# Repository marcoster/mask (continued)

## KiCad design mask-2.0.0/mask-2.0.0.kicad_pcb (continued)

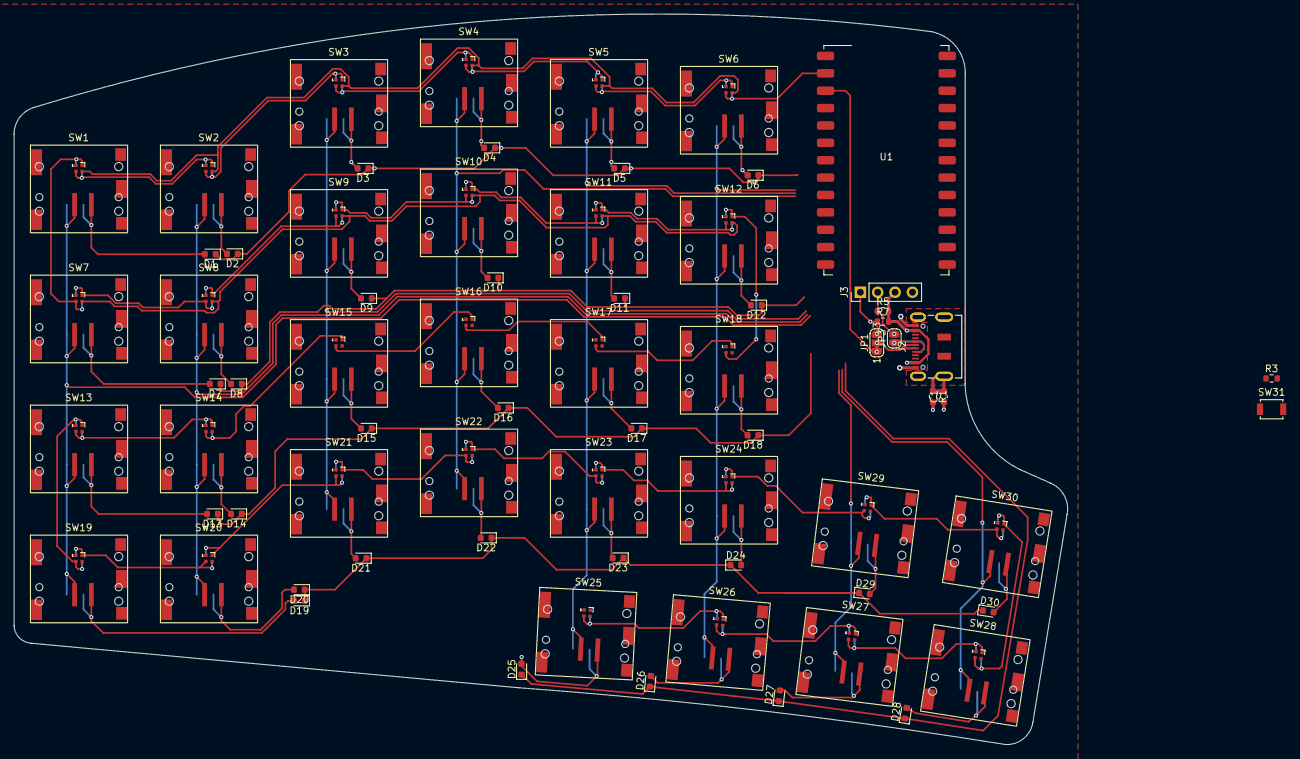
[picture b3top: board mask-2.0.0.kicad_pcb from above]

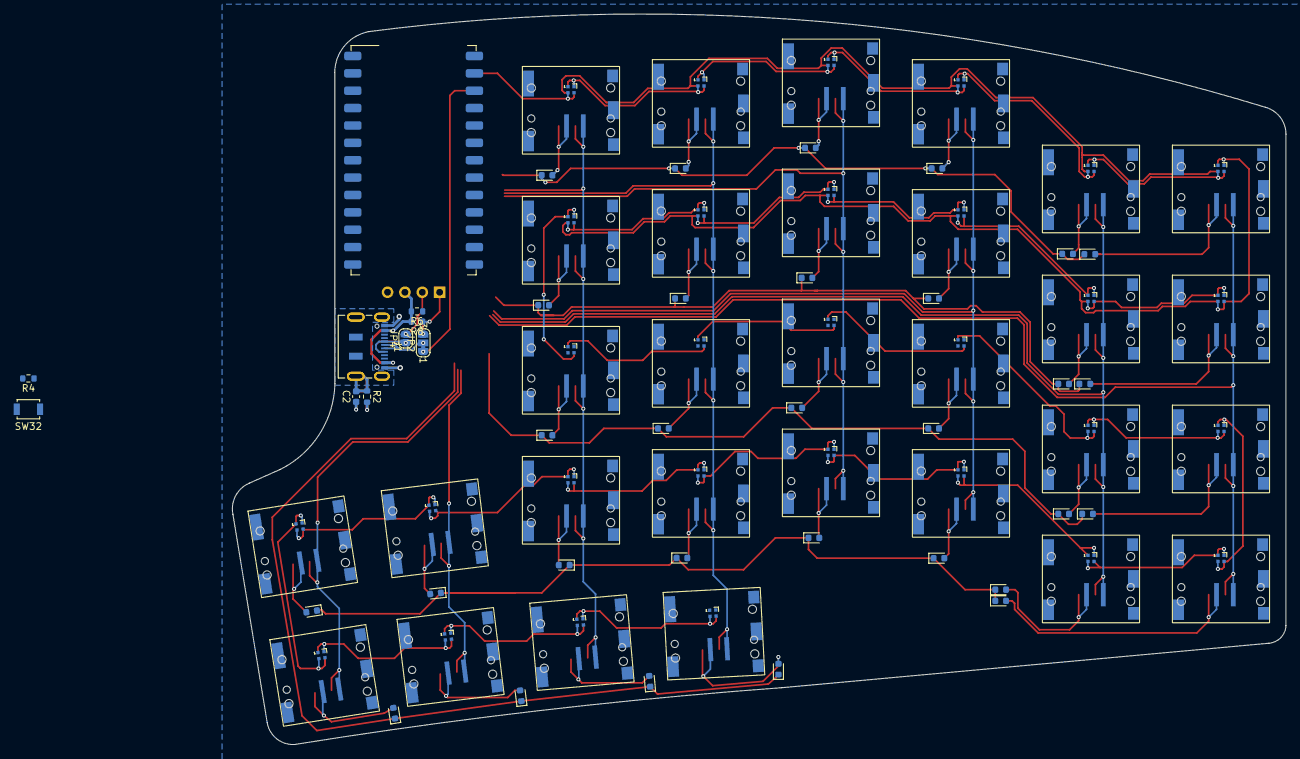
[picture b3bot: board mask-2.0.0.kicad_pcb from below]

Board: 2 copper layers, 154.0 x 106.8 mm, 80 parts (9 on the bottom side), 83 nets.

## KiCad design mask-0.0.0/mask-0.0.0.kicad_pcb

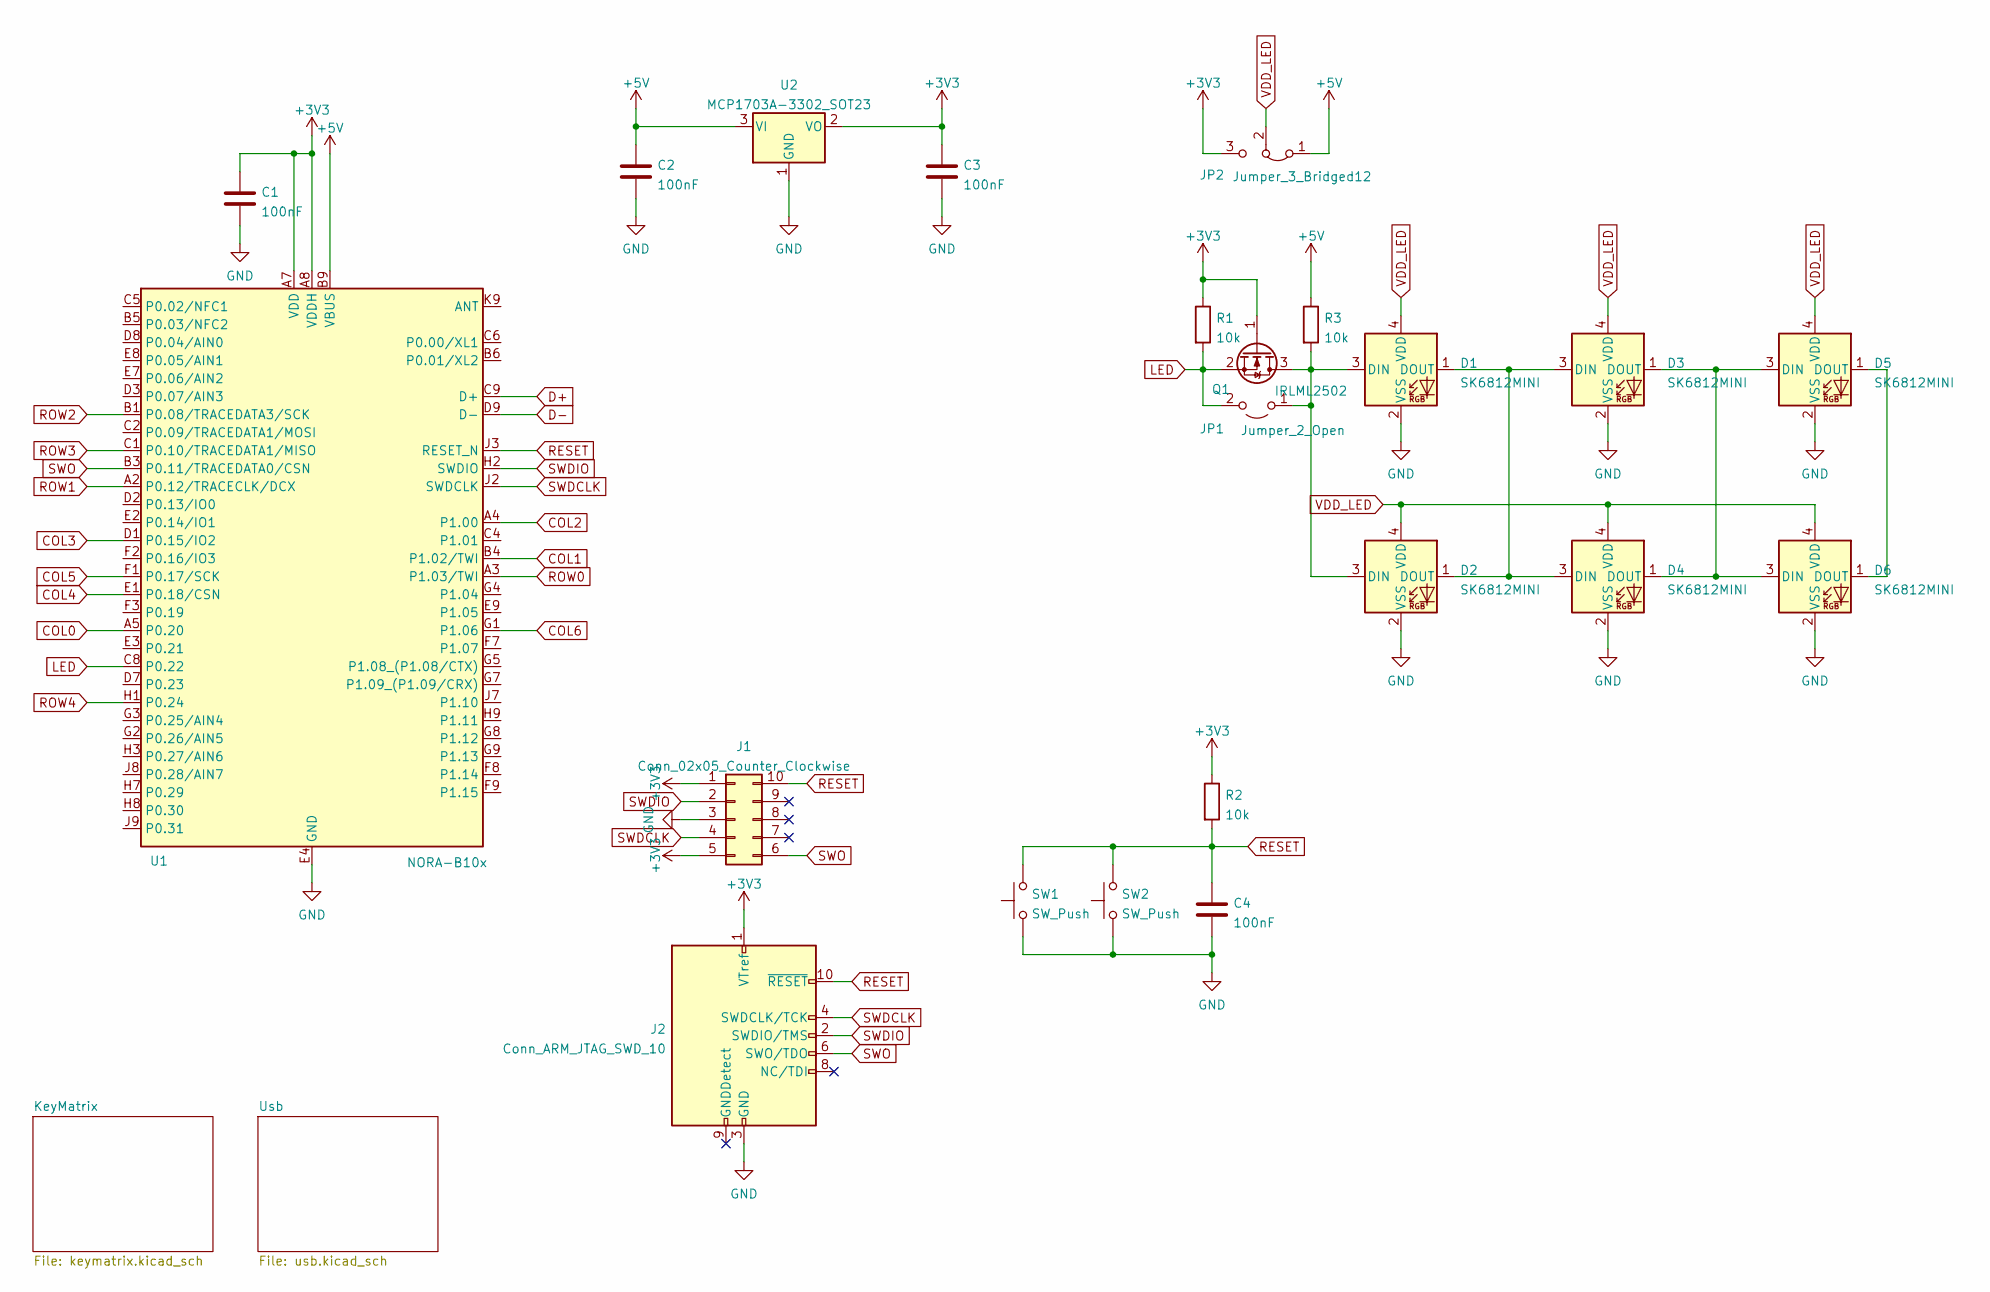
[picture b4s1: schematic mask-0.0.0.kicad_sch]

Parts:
C1, C2, C3, C4: 100nF; C_0603_1608Metric
D1, D2, D3, D4, D5, D6: SK6812MINI; LED_SK6812MINI_PLCC4_3.5x3.5mm_P1.75mm
J1: Conn_02x05_Counter_Clockwise; Tag-Connect_TC2050-IDC-NL_2x05_P1.27mm_Vertical
J2: Conn_ARM_JTAG_SWD_10; PinHeader_2x05_P1.27mm_Vertical_SMD
JP1: Jumper_2_Open; SolderJumper-2_P1.3mm_Open_RoundedPad1.0x1.5mm
JP2: Jumper_3_Bridged12; SolderJumper-3_P1.3mm_Bridged12_RoundedPad1.0x1.5mm
Q1: IRLML2502; SOT-23
R1, R2, R3: 10k; R_0603_1608Metric
SW1, SW2: SW_Push; SW_SPST_B3U-1000P
U1: NORA-B10x; Ublox_NORA-B10x
U2: MCP1703A-3302_SOT23; SOT-23

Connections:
+3V3: C1.1, C3.1, J1.1, J1.5, J2.1 (VTref), JP2.3 (B), Q1.1 (G), R1.1, R2.1, U1.A7 (VDD), U1.A8 (VDDH), U1.B7 (VDD), U2.2 (VO)
+5V: C2.1, JP2.1 (A), R3.1, U1.B9 (VBUS), U2.3 (VI); also elsewhere on the board
COL0: U1.A5 (P0.20); also elsewhere on the board
COL1: U1.B4 (P1.02/TWI); also elsewhere on the board
COL2: U1.A4 (P1.00); also elsewhere on the board
COL3: U1.D1 (P0.15/IO2); also elsewhere on the board
COL4: U1.E1 (P0.18/CSN); also elsewhere on the board
COL5: U1.F1 (P0.17/SCK); also elsewhere on the board
COL6: U1.G1 (P1.06); also elsewhere on the board
D+: U1.C9 (D+); also elsewhere on the board
D-: U1.D9 (D-); also elsewhere on the board
GND: C1.2, C2.2, C3.2, C4.2, D1.2 (VSS), D2.2 (VSS), D3.2 (VSS), D4.2 (VSS), D5.2 (VSS), D6.2 (VSS), J1.3, J2.3 (GND), J2.5 (GND), SW1.1, SW2.1, U1.A1 (GND), U1.A9 (GND), U1.B2 (GND), U1.B8 (GND), U1.E4 (GND), U1.E5 (GND), U1.F4 (GND), U1.F5 (GND), U1.K2 (GND), U1.K3 (GND), U1.K5 (GND), U1.K7 (GND), U1.K8 (GND), U1.L1 (GND), U1.L9 (GND), U1.M1 (GND), U1.M2 (GND), U1.M8 (GND), U1.M9 (GND), U2.1 (GND); also elsewhere on the board
LED: JP1.2 (B), Q1.2 (S), R1.2, U1.C8 (P0.22)
unnamed: D1.1 (DOUT), D2.1 (DOUT), D3.3 (DIN), D4.3 (DIN)
unnamed: D1.3 (DIN), D2.3 (DIN), JP1.1 (A), Q1.3 (D), R3.2
unnamed: D3.1 (DOUT), D4.1 (DOUT), D5.3 (DIN), D6.3 (DIN)
unnamed: D5.1 (DOUT), D6.1 (DOUT)
RESET: C4.1, J1.10, J2.10 (~RESET), R2.2, SW1.2, SW2.2, U1.J3 (RESET_N)
ROW0: U1.A3 (P1.03/TWI); also elsewhere on the board
ROW1: U1.A2 (P0.12/TRACECLK/DCX); also elsewhere on the board
ROW2: U1.B1 (P0.08/TRACEDATA3/SCK); also elsewhere on the board
ROW3: U1.C1 (P0.10/TRACEDATA1/MISO); also elsewhere on the board
ROW4: U1.H1 (P0.24); also elsewhere on the board
SWDCLK: J1.4, J2.4 (SWDCLK/TCK), U1.J2 (SWDCLK)
SWDIO: J1.2, J2.2 (SWDIO/TMS), U1.H2 (SWDIO)
SWO: J1.6, J2.6 (SWO/TDO), U1.B3 (P0.11/TRACEDATA0/CSN)
VDD_LED: D1.4 (VDD), D2.4 (VDD), D3.4 (VDD), D4.4 (VDD), D5.4 (VDD), D6.4 (VDD), JP2.2 (C)

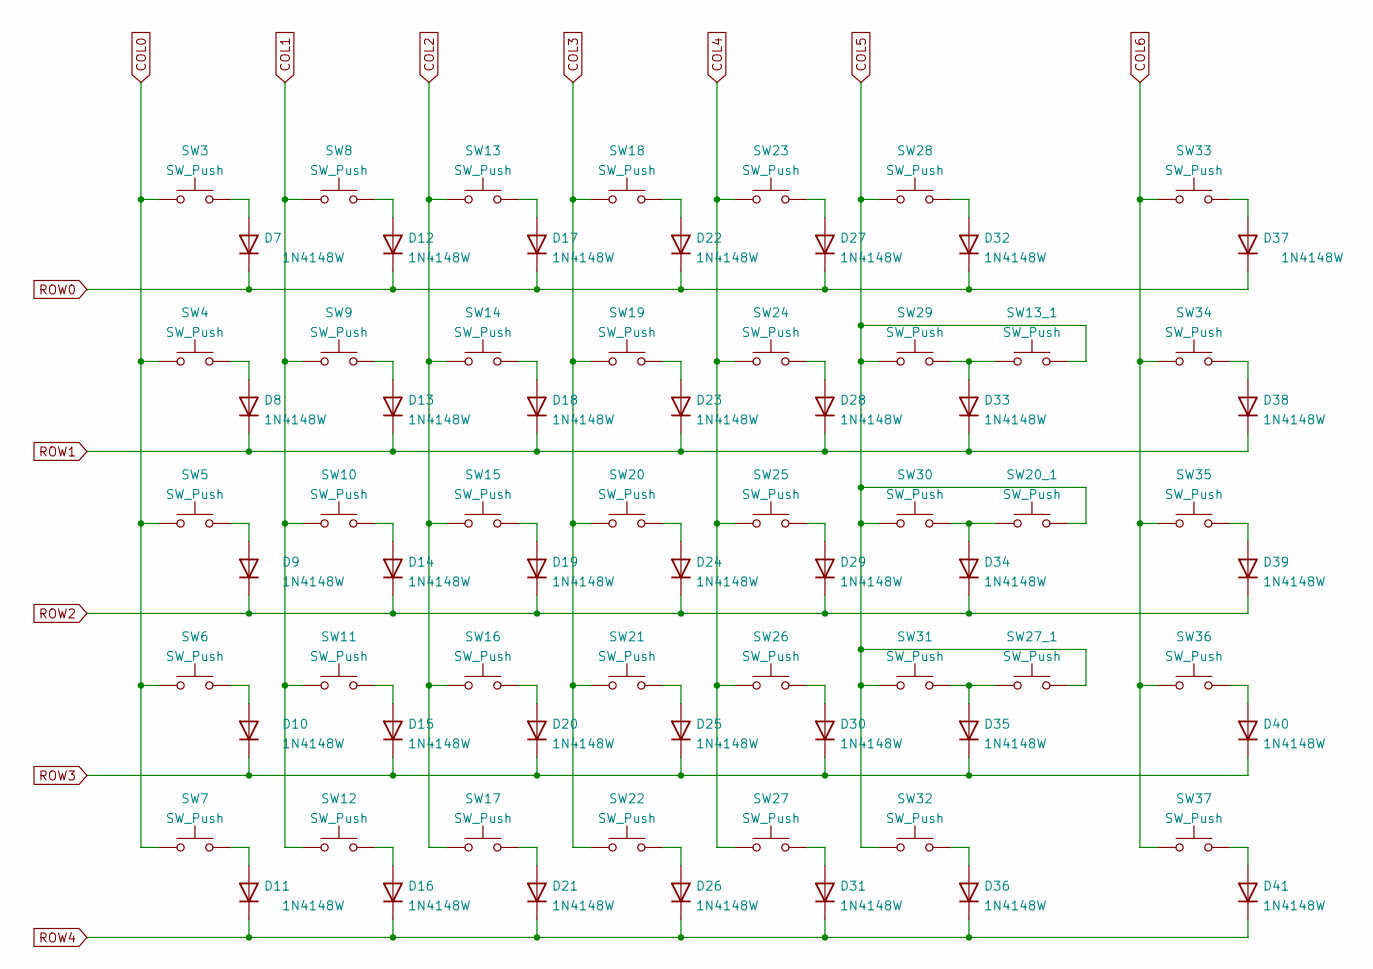
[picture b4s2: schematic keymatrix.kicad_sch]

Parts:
D7, D8, D9, D10, D11, D12, D13, D14, D15, D16, D17, D18, D19, D20, D21, D22, D23, D24, D25, D26, D27, D28, D29, D30, D31, D32, D33, D34, D35, D36, D37, D38, D39, D40, D41: 1N4148W; D_SOD-123_TopBottom
SW3, SW4, SW5, SW6, SW7, SW8, SW9, SW10, SW11, SW12, SW13, SW14, SW15, SW16, SW18, SW19, SW20, SW21, SW22, SW23, SW24, SW25, SW26, SW27, SW28, SW29, SW30, SW31, SW32, SW33, SW34, SW35, SW36, SW37: SW_Push; SW_Cherry_MX_1.00u_Kailh_Socket_TopBottom
SW13_1, SW20_1, SW27_1: SW_Push; SW_Cherry_MX_2.00u_Kailh_Socket_NoStabilizer_TopBottom
SW17: SW_Push; SW_Cherry_MX_1.25u_Kailh_Socket_TopBottom

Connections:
COL0: SW3.1, SW4.1, SW5.1, SW6.1, SW7.1; also elsewhere on the board
COL1: SW8.1, SW9.1, SW10.1, SW11.1, SW12.1; also elsewhere on the board
COL2: SW13.1, SW14.1, SW15.1, SW16.1, SW17.1; also elsewhere on the board
COL3: SW18.1, SW19.1, SW20.1, SW21.1, SW22.1; also elsewhere on the board
COL4: SW23.1, SW24.1, SW25.1, SW26.1, SW27.1; also elsewhere on the board
COL5: SW13_1.2, SW20_1.2, SW27_1.2, SW28.1, SW29.1, SW30.1, SW31.1, SW32.1; also elsewhere on the board
COL6: SW33.1, SW34.1, SW35.1, SW36.1, SW37.1; also elsewhere on the board
unnamed: D7.2 (A), SW3.2
unnamed: D8.2 (A), SW4.2
unnamed: D9.2 (A), SW5.2
unnamed: D10.2 (A), SW6.2
unnamed: D11.2 (A), SW7.2
unnamed: D12.2 (A), SW8.2
unnamed: D13.2 (A), SW9.2
unnamed: D14.2 (A), SW10.2
unnamed: D15.2 (A), SW11.2
unnamed: D16.2 (A), SW12.2
unnamed: D17.2 (A), SW13.2
unnamed: D18.2 (A), SW14.2
unnamed: D19.2 (A), SW15.2
unnamed: D20.2 (A), SW16.2
unnamed: D21.2 (A), SW17.2
unnamed: D22.2 (A), SW18.2
unnamed: D23.2 (A), SW19.2
unnamed: D24.2 (A), SW20.2
unnamed: D25.2 (A), SW21.2
unnamed: D26.2 (A), SW22.2
unnamed: D27.2 (A), SW23.2
unnamed: D28.2 (A), SW24.2
unnamed: D29.2 (A), SW25.2
unnamed: D30.2 (A), SW26.2
unnamed: D31.2 (A), SW27.2
unnamed: D32.2 (A), SW28.2
unnamed: D33.2 (A), SW13_1.1, SW29.2
unnamed: D34.2 (A), SW20_1.1, SW30.2
unnamed: D35.2 (A), SW27_1.1, SW31.2
unnamed: D36.2 (A), SW32.2
unnamed: D37.2 (A), SW33.2
unnamed: D38.2 (A), SW34.2
unnamed: D39.2 (A), SW35.2
unnamed: D40.2 (A), SW36.2
unnamed: D41.2 (A), SW37.2
ROW0: D7.1 (K), D12.1 (K), D17.1 (K), D22.1 (K), D27.1 (K), D32.1 (K), D37.1 (K); also elsewhere on the board
ROW1: D8.1 (K), D13.1 (K), D18.1 (K), D23.1 (K), D28.1 (K), D33.1 (K), D38.1 (K); also elsewhere on the board
ROW2: D9.1 (K), D14.1 (K), D19.1 (K), D24.1 (K), D29.1 (K), D34.1 (K), D39.1 (K); also elsewhere on the board
ROW3: D10.1 (K), D15.1 (K), D20.1 (K), D25.1 (K), D30.1 (K), D35.1 (K), D40.1 (K); also elsewhere on the board
ROW4: D11.1 (K), D16.1 (K), D21.1 (K), D26.1 (K), D31.1 (K), D36.1 (K), D41.1 (K); also elsewhere on the board

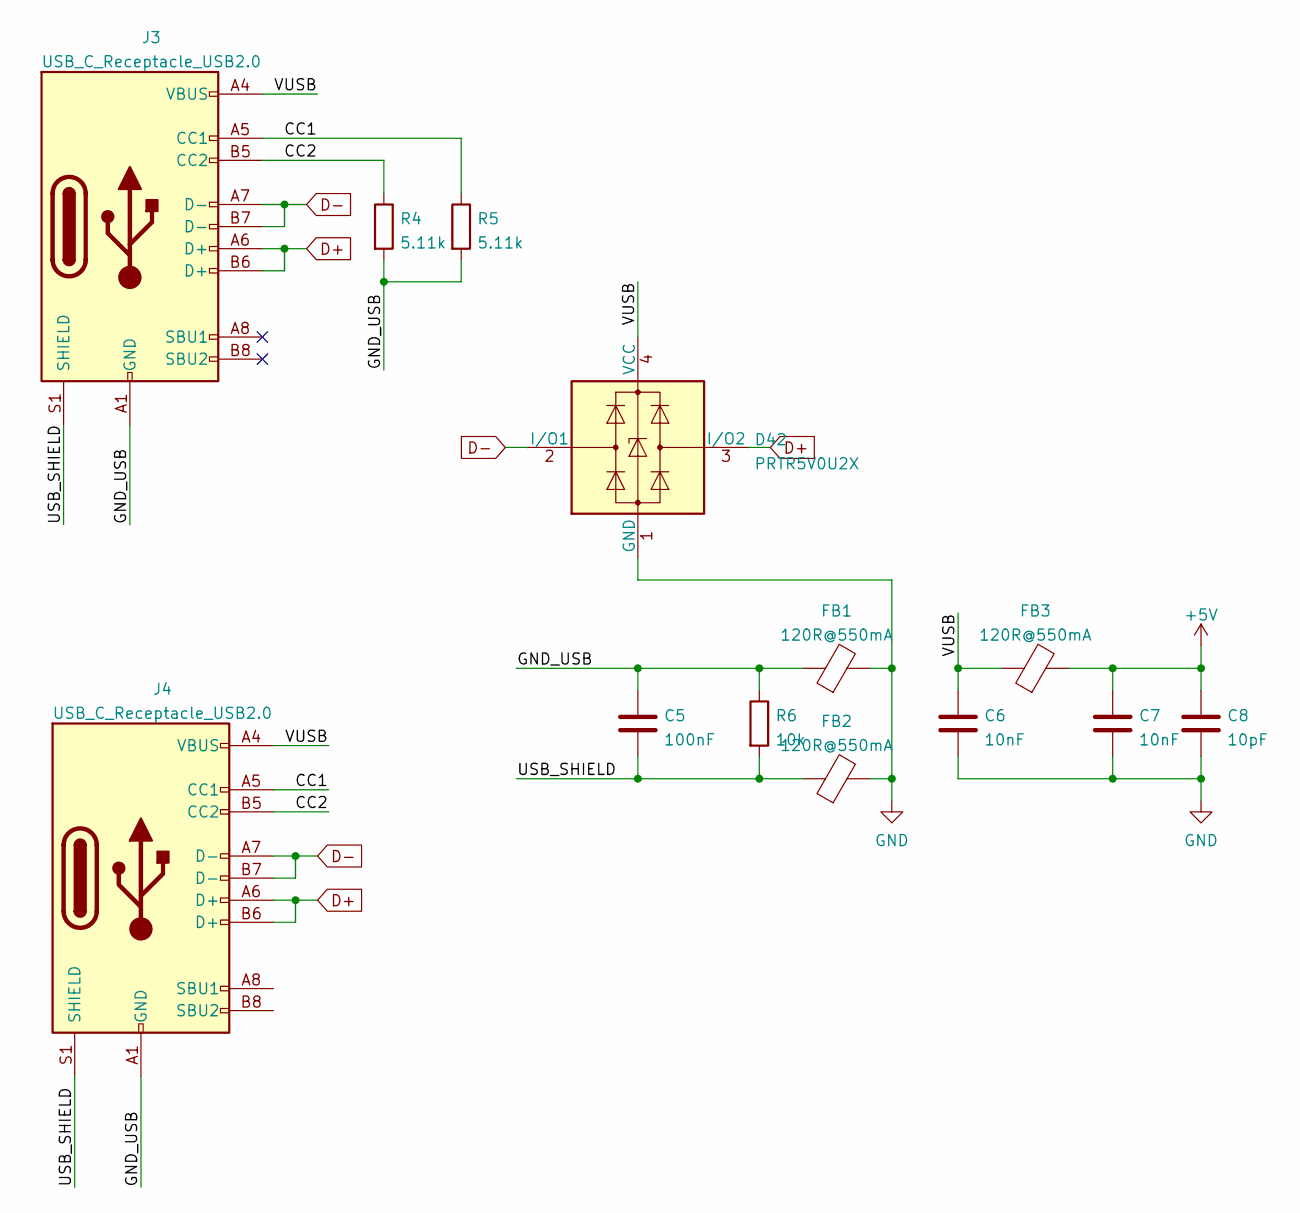
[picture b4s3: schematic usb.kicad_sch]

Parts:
C5: 100nF; C_0603_1608Metric
C6, C7: 10nF; C_0603_1608Metric
C8: 10pF; C_0603_1608Metric
D42: PRTR5V0U2X; SOT-143
FB1, FB2, FB3: 120R@550mA; R_0603_1608Metric
J3, J4: USB_C_Receptacle_USB2.0; USB_C_Receptacle_JAE_DX07S016JA1R1500
R4, R5: 5.11k; R_0603_1608Metric
R6: 10k; R_0603_1608Metric

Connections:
+5V: C7.1, C8.1, FB3.2; also elsewhere on the board
/Usb/CC1: J3.A5 (CC1), J4.A5 (CC1), R5.1
/Usb/CC2: J3.B5 (CC2), J4.B5 (CC2), R4.1
/Usb/GND_USB: C5.1, FB1.1, J3.A1 (GND), J3.A12 (GND), J3.B1 (GND), J3.B12 (GND), J4.A1 (GND), J4.A12 (GND), J4.B1 (GND), J4.B12 (GND), R4.2, R5.2, R6.1
/Usb/USB_SHIELD: C5.2, FB2.1, J3.S1 (SHIELD), J4.S1 (SHIELD), R6.2
/Usb/VUSB: C6.1, D42.4 (VCC), FB3.1, J3.A4 (VBUS), J3.A9 (VBUS), J3.B4 (VBUS), J3.B9 (VBUS), J4.A4 (VBUS), J4.A9 (VBUS), J4.B4 (VBUS), J4.B9 (VBUS)
D+: D42.3 (I/O2), J3.A6 (D+), J3.B6 (D+), J4.A6 (D+), J4.B6 (D+); also elsewhere on the board
D-: D42.2 (I/O1), J3.A7 (D-), J3.B7 (D-), J4.A7 (D-), J4.B7 (D-); also elsewhere on the board
GND: C6.2, C7.2, C8.2, D42.1 (GND), FB1.2, FB2.2; also elsewhere on the board

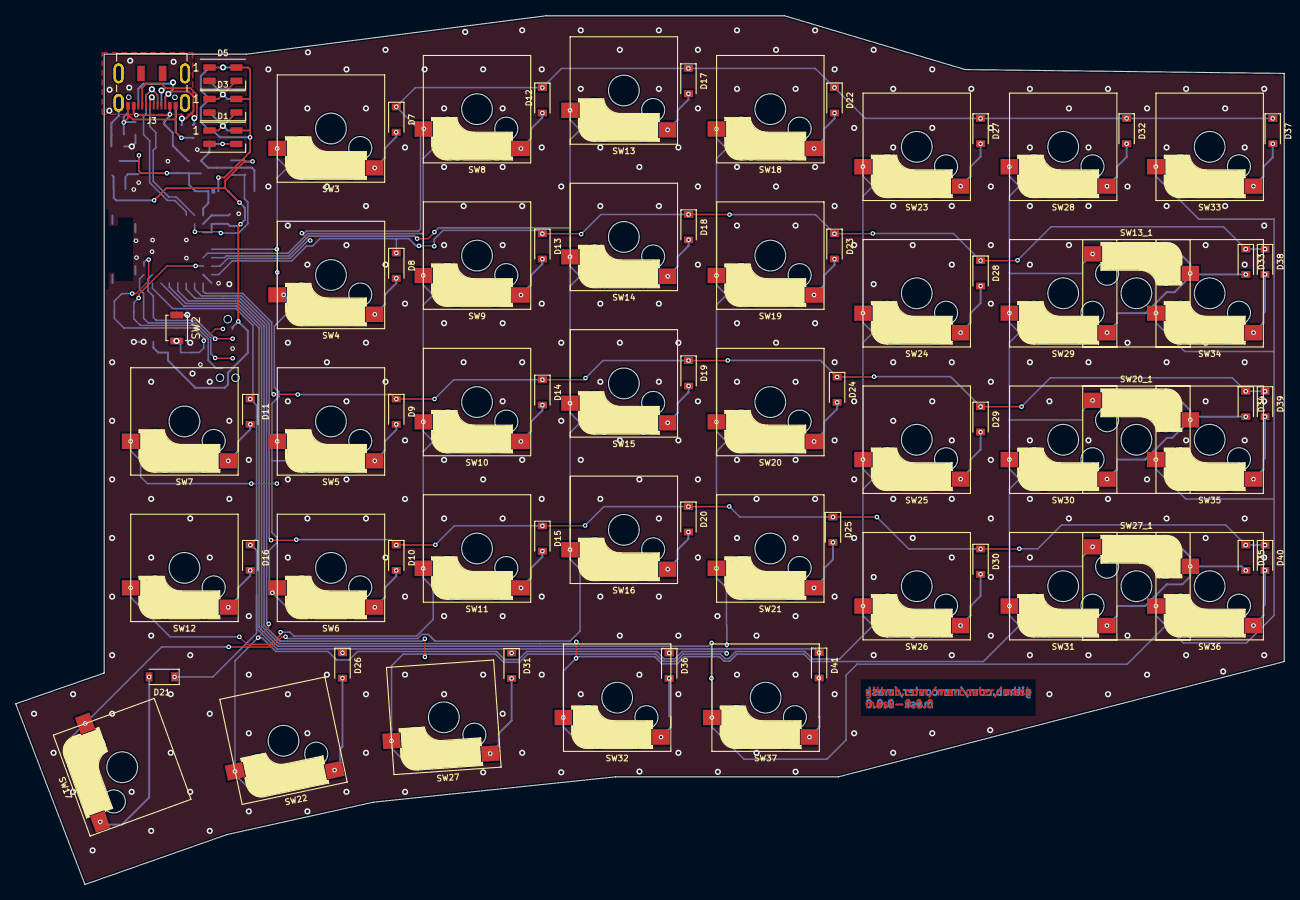
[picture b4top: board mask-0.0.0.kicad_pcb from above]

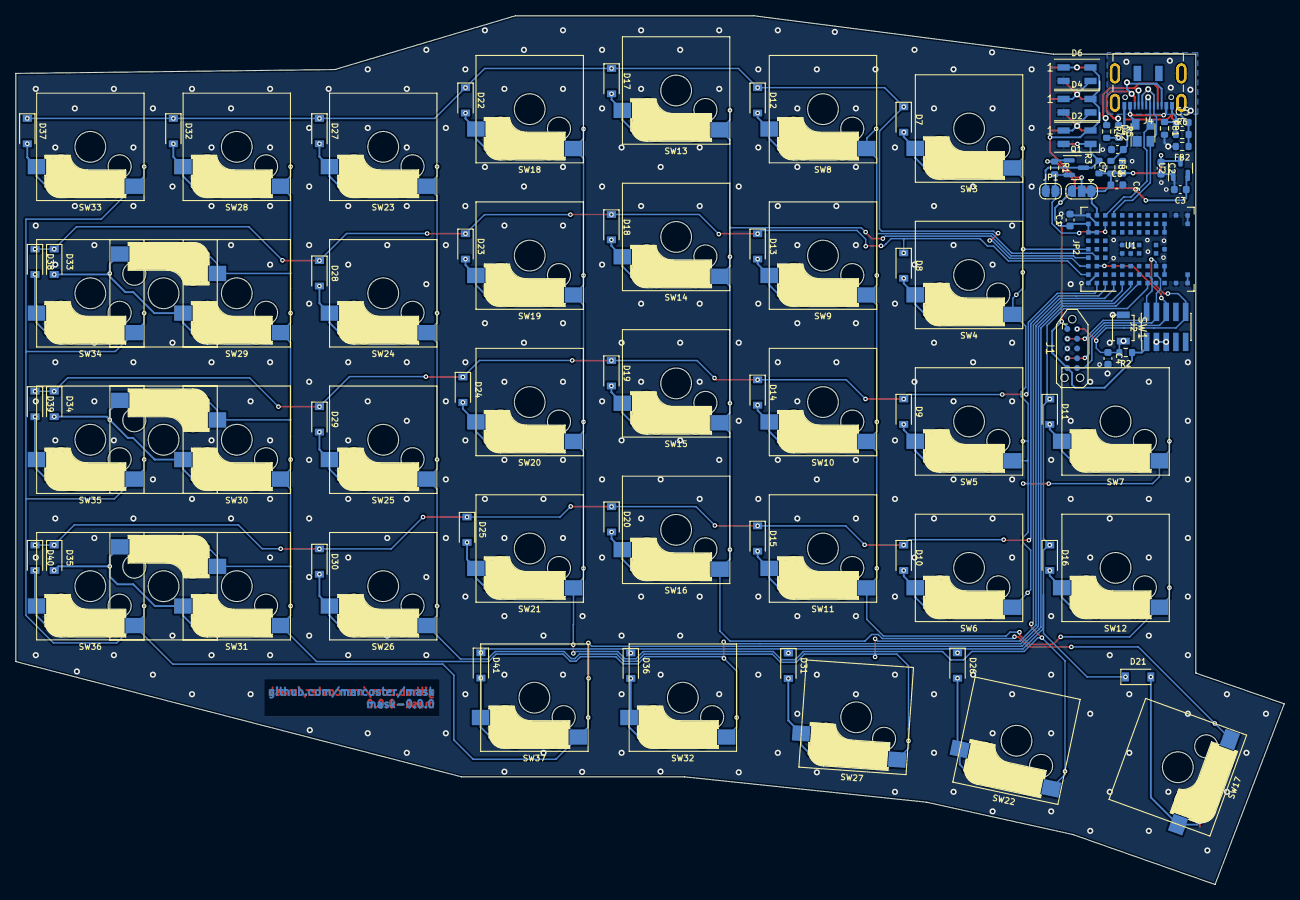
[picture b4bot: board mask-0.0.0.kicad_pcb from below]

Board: 2 copper layers, 165.0 x 113.0 mm, 108 parts (30 on the bottom side), 67 nets.

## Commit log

2021-10-08 create project
2021-10-11 copy cherry mx libs for Kailh Socket mod
2021-10-11 cherry-mx kailh socket: update footprints for sockets
2021-10-11 draw basic key-matrix
2021-10-12 diodes: add package with top/bottom mounting
2021-10-12 change diodes package, start test positioning in correct distance
2021-10-13 switch: add 2.00u switch without stabilizer
2021-10-13 remove pcb-holes from packages
2021-10-13 test-place buttons (only ortholinear, not shifted)
2021-10-13 first test layout
2021-10-13 add key-frame cutout onto User.Comment layer
2021-10-15 small changes
2021-11-05 0.0.0: create symbol/footprint for ble module, some schematic progress
2021-11-08 schematic: connect debugger
2021-11-09 add leds (sk2812) and level converter
2021-11-12 udpate routing
2021-11-18 mask-0.0.0: begin of matrix routing
2021-11-18 mask-0.0.0: routed
2021-11-18 mask-0.0.0: correct pcb
2021-11-19 mask-0.0.0: optimize routing, via stitching
2021-11-19 mask-0.0.0: add text to copper, change fill-zone parameter
2022-11-29 mask-1.0.0: copy files from sofle repo
2022-11-29 mask-2.0.0: begin schematic and mx ulp package
2022-12-01 mask-2.0.0: basic schematic, start cleaning up the ratsnets
2022-12-02 mask: backup full 60 key schematic maybe for a future revival
2022-12-02 mask-2.0.0: update to smd kb2040 variant
2022-12-02 mask-2.0.0: correct smd footprint of kb2040
2022-12-02 mask-2.0.0: first layout prototype
2022-12-03 mask-2.0.0: routing halfway done, 3.3v for led's next
2022-12-05 mask-2.0.0: finalize routing
2023-03-20 module-version 0.0.0: starting schematic and layout positioning
2023-03-21 module-0.0.0: begin bmd-380 symbol and footprint
2023-03-21 bmd-380 footprint: finalize
2023-03-21 mask-module-0.0.0: update schematic
2023-03-27 module-0.0.0: add footprint for usb
2023-03-27 module-0.0.0: more shematic work
2023-03-27 module-0.0.0: basic positioning
2023-03-28 module-0.0.0: finish pcb
2026-02-26 mask-1.1.0: pcb done
2026-03-06 mask-1.1.0: add 3d models of hotswap sockets on both sides
